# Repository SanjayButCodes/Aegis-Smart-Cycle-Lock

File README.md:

# Aegis Smart Cycle Lock
Aegis is a heavy-duty, open-source, distributed smart bicycle lock. Unlike standard commercial locks, Aegis uses a split-node architecture to physically separate the user interface from the vulnerable locking mechanism, making it highly resistant to tampering and brute-force attacks.

🏗️ System Architecture

The system consists of two custom-designed nodes connected by a weather-sealed Cat5e bridge cable:

The Handlebar Hub (User Interface): A compact, IP65-rated pod mounted to the handlebars. It contains an Arduino Nano, an NFC card reader, an RGB status LED, and a locking button. It operates purely on 5V logic.

The Armored Rear Hub (The Brain & Brawn): A heavy-duty horseshoe frame lock mounted over the rear tire. It houses the ESP32 brain, a 12V worm-gear motor, a 3S battery pack, a 110dB siren, and an IMU accelerometer for theft detection.

The "Dead-Man Loop" Tamper Trace

A continuous 3.3V continuity loop originates at the Rear Hub, travels up the Cat5e cable, and traces the exact outer physical perimeter of the Handlebar Hub PCB. If a thief cuts the communication cable or attempts to crack open the Handlebar enclosure, the circuit breaks and the Rear Hub instantly triggers the 110dB siren.

⚡ Hardware Specifications

Armored Rear Hub (Main PCB)

Microcontroller: ESP32-WROOM-32U (Requires external antenna)

Power Supply: 3S (11.1V-12.6V) 18650 Battery Pack

Charging: IP2326 3S Type-C BMS charging IC

Logic Power: MP2315 Buck Converter (Steps 12.6V down to clean 3.3V)

Motor Driver: DRV8871 H-Bridge (Handling up to 2A stall current)

Actuator: JGY370 12V Worm Gear Motor

Sensors: MPU6050 Accelerometer (Wired to ESP32 ext0 wake interrupt)

Audio: 5V Active Piezo Siren

Handlebar Hub (UI PCB)

Microcontroller: Arduino Nano (DIP-30)

Authentication: PN532 NFC/RFID Module (I2C)

User Input: 12mm Waterproof Momentary Push Button

Feedback: Common Cathode RGB LED

Communication: 9600-baud UART over Cat5e Bridge

🛠️ Mechanical & CAD Design

The physical enclosures are designed to be FDM 3D-printed in highly impact-resistant materials like PETG, ABS, or Polycarbonate.

The Deadbolt: The locking mechanism uses a 12mm hardened steel rod acting as a deadbolt.

Rack and Pinion: The JGY370 motor drives a Module 1.5 pinion gear, converting rotational torque into linear motion to slide the deadbolt across the rear tire spokes.

Limit Switches: Two KW12-3 micro limit switches are installed at the ends of the deadbolt track to cut motor power precisely when fully locked or fully unlocked, preventing gear stripping.

Weatherproofing: The enclosures utilize overlapping lap joints designed to hold TPU gaskets or silicone bead seals to protect against rain and tire splash.

💻 Firmware & Software

The codebase is split into two environments:

/firmware/handlebar_nano/: Runs a non-blocking loop polling the PN532 for authorized MIFARE tags. Upon reading a tag or button press, it transmits a clean UART string (e.g., CMD:UNLOCK:UID) down to the rear hub.

/firmware/rear_esp32/: The central state machine. It manages the DRV8871 motor phases, parses UART commands, and handles extreme power conservation.

Deep Sleep Architecture

To allow the lock to run for months on a single charge, the ESP32 enters deep sleep immediately upon locking. It consumes only ~10µA until the MPU6050 accelerometer detects physical tampering, which triggers a hardware interrupt on GPIO 25, waking the ESP32 instantly to sound the alarm.

⚠️ High-Current Safety Warning

This project drives a high-torque 12V motor capable of drawing up to 2 Amps when stalled against a jammed lock.

PCB Routing: The VBAT and MOTOR nets on the Rear Hub PCB must be routed at a minimum of 4.0mm trace width.

Battery: Only use protected 3S battery packs with an integrated BMS. Never run standard 1S cells in series without balancing protection.

🚀 Getting Started

(Instructions for ordering PCBs, flashing code, and assembling the CAD files will be added here as the final manufacturing files are released.)

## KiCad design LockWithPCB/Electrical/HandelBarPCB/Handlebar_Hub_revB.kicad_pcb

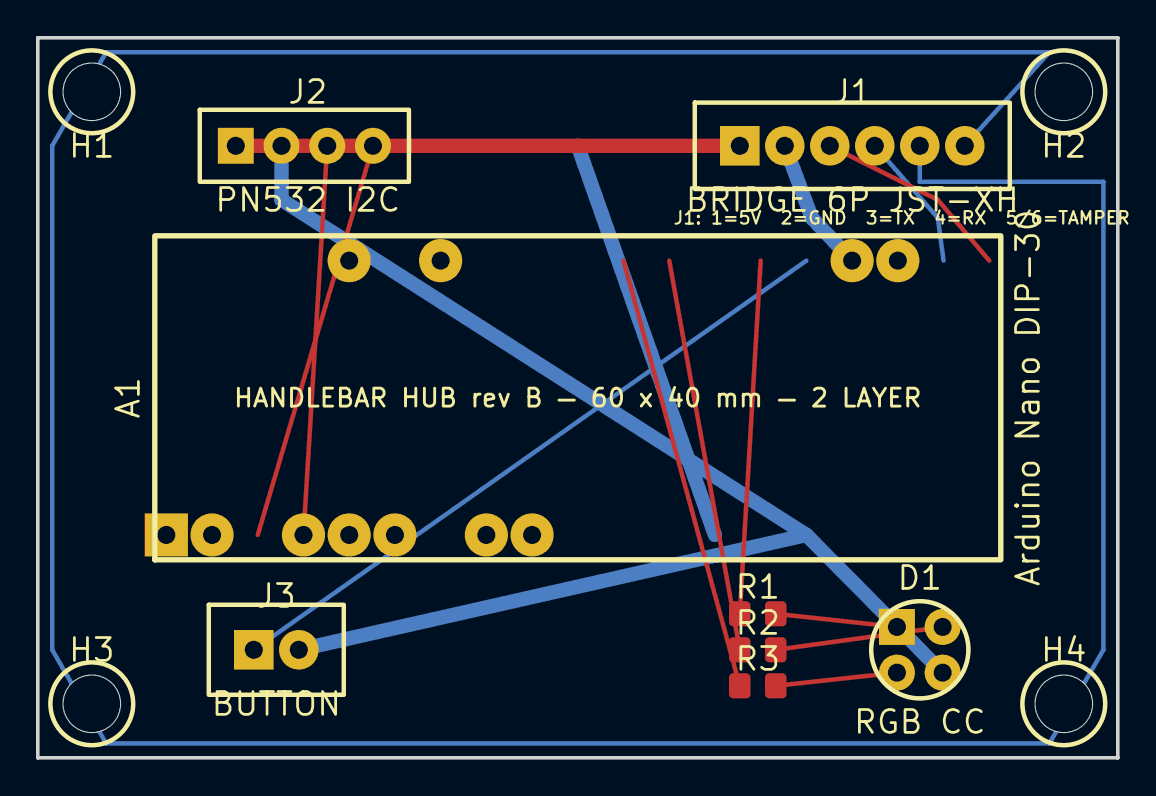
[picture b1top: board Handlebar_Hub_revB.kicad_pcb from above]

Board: 2 copper layers, 60.0 x 40.0 mm, 12 parts (0 on the bottom side), 14 nets.

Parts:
A1: Arduino Nano DIP-30; Arduino_Nano
D1: RGB CC; LED_D5.0mm-4_RGB_Staggered_Pins
H1, H2, H3, H4: M3 NPTH; MountingHole_3.2mm_NPTH
J1: BRIDGE 6P JST-XH; JST_XH_B2B-XH-A_1x06_P2.50mm_Vertical
J2: PN532 I2C; PinSocket_1x04_P2.54mm_Vertical
J3: BUTTON; JST_XH_B2B-XH-A_1x02_P2.50mm_Vertical
R1, R2, R3: 220R; R_0805_2012Metric

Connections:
+5V: A1.27, J1.1, J2.1
BUTTON_N: A1.5, J3.1
GND: A1.4, A1.29, D1.4, J1.2, J2.2, J3.2
I2C_SCL: A1.17, J2.4
I2C_SDA: A1.18, J2.3
LED_B: D1.3, R3.2
LED_B_RAW: A1.9, R3.1
LED_G: D1.2, R2.2
LED_G_RAW: A1.8, R2.1
LED_R: D1.1, R1.2
LED_R_RAW: A1.6, R1.1
TAMPER_LOOP: J1.5, J1.6
UART_RX: A1.2, J1.4
UART_TX: A1.1, J1.3

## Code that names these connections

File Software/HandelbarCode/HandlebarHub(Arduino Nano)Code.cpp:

#include <Wire.h>
#include <Adafruit_PN532.h>

// Hardware Pin Definitions based on PCB Rev B
#define LOCK_BUTTON_PIN 2   // Mapped to Nano D2
#define LED_R_PIN 3         // Mapped to Nano D3
#define LED_G_PIN 5         // Mapped to Nano D5
#define LED_B_PIN 6         // Mapped to Nano D6

// PN532 I2C Setup (using hardware I2C pins A4/A5)
#define PN532_IRQ   (4)     // Abstracted IRQ
#define PN532_RESET (7)     // Abstracted Reset
Adafruit_PN532 nfc(PN532_IRQ, PN532_RESET);

void setup() {
  // Initialize UART bridge to ESP32 (Hardware Serial D0/D1)
  Serial.begin(9600); 
  
  pinMode(LOCK_BUTTON_PIN, INPUT_PULLUP);
  pinMode(LED_R_PIN, OUTPUT);
  pinMode(LED_G_PIN, OUTPUT);
  pinMode(LED_B_PIN, OUTPUT);

  nfc.begin();
  if (!nfc.getFirmwareVersion()) {
    while (1); // Halt if PN532 is missing
  }
  nfc.SAMConfig(); // Configure PN532 to read RFID tags
  setLED(0, 255, 0); // Boot to Green (Unlocked)
}

void loop() {
  // 1. Check for physical Lock Button press
  if (digitalRead(LOCK_BUTTON_PIN) == LOW) {
    Serial.println("CMD:LOCK");
    setLED(255, 0, 0); // Red
    delay(1000); // Software debounce
  }

  // 2. Poll NFC Reader (with 50ms timeout to keep loop non-blocking)
  uint8_t success;
  uint8_t uid[] = { 0, 0, 0, 0, 0, 0, 0 };
  uint8_t uidLength;
  
  success = nfc.readPassiveTargetID(PN532_MIFARE_ISO14443A, uid, &uidLength, 50);
  
  if (success) {
    Serial.print("CMD:UNLOCK:");
    for (uint8_t i = 0; i < uidLength; i++) {
      if (uid[i] <= 0x0F) Serial.print("0"); // Pad with leading zero
      Serial.print(uid[i], HEX);
    }
    Serial.println();
    setLED(0, 255, 0); // Green
    delay(1000); // Prevent spamming payload
  }
}

void setLED(int r, int g, int b) {
  analogWrite(LED_R_PIN, r);
  analogWrite(LED_G_PIN, g);
  analogWrite(LED_B_PIN, b);
}
